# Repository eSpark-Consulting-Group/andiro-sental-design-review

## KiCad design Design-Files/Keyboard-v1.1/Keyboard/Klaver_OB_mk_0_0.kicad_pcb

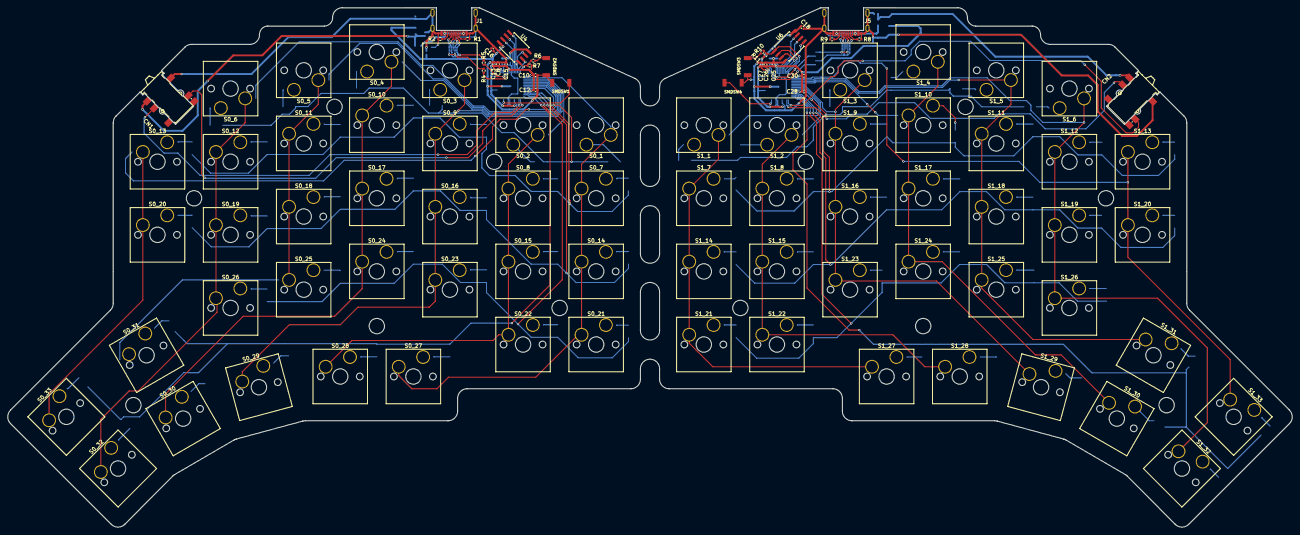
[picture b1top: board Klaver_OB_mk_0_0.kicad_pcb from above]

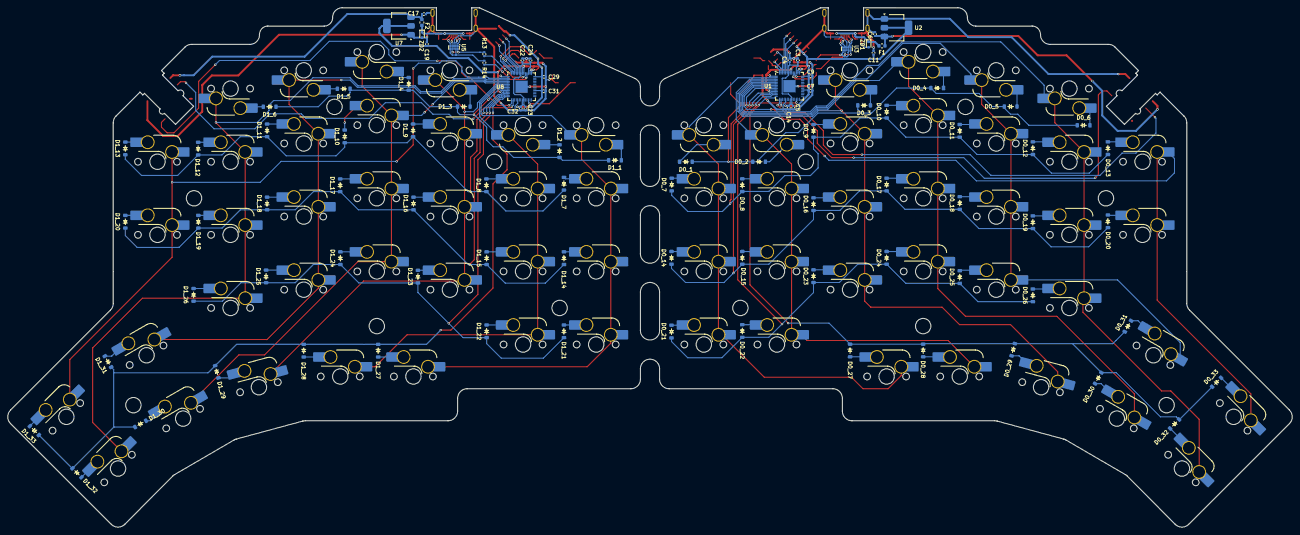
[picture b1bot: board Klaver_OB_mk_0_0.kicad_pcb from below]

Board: 2 copper layers, 334.7 x 135.3 mm, 192 parts (160 on the bottom side), 132 nets.

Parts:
C3, C4, C7, C9, C10, C12, C13, C14, C15, C22, C23, C25, C27, C28, C29, C30, C31, C32: 100n; C_0402_1005Metric
C5, C8, C16, C18, C24, C26: 1u; C_0402_1005Metric
C6, C11, C17, C19: 10u; C_0402_1005Metric
CN1, CN2: PJ-399F-6A; AUDIO-SMD_PJ-399F-6A
D0_1, D0_2, D0_3, D0_4, D0_5, D0_6, D0_7, D0_8, D0_9, D0_10, D0_11, D0_12, D0_13, D0_14, D0_15, D0_16, D0_17, D0_18, D0_19, D0_20, D0_21, D0_22, D0_23, D0_24, D0_25, D0_26, D0_27, D0_28, D0_29, D0_30, D0_31, D0_32, D0_33, D1_1, D1_2, D1_3, D1_4, D1_5, D1_6, D1_7, D1_8, D1_9, D1_10, D1_11, D1_12, D1_13, D1_14, D1_15, D1_16, D1_17, D1_18, D1_19, D1_20, D1_21, D1_22, D1_23, D1_24, D1_25, D1_26, D1_27, D1_28, D1_29, D1_30, D1_31, D1_32, D1_33: Diode; Diode_SOD-123
F1, F2: BSMD0603-050-12V; Fuse_0603_1608Metric
J1, J5: TYPE-C-31-M-13C
R1, R2, R8, R9: 5.1k; R_0402_1005Metric
R4, R5, R13, R14: 27; R_0402_1005Metric
R6, R10: 1k; R_0402_1005Metric
R7, R11: 10k; R_0402_1005Metric
S0_1, S0_2, S0_3, S0_4, S0_5, S0_6, S0_7, S0_8, S0_9, S0_10, S0_11, S0_12, S0_13, S0_14, S0_15, S0_16, S0_17, S0_18, S0_19, S0_20, S0_21, S0_22, S0_23, S0_24, S0_25, S0_26, S0_27, S0_28, S0_29, S0_30, S0_31, S0_32, S0_33, S1_1, S1_2, S1_3, S1_4, S1_5, S1_6, S1_7, S1_8, S1_9, S1_10, S1_11, S1_12, S1_13, S1_14, S1_15, S1_16, S1_17, S1_18, S1_19, S1_20, S1_21, S1_22, S1_23, S1_24, S1_25, S1_26, S1_27, S1_28, S1_29, S1_30, S1_31, S1_32, S1_33: Keyswitch; Hotswap_MX_Plated_1.00u
SMDSW1, SMDSW2, SMDSW3, SMDSW4: TS-1088R-02026
U1, U8: RP2040; QFN-56-1EP_7x7mm_P0.4mm_EP3.2x3.2mm
U2, U7: NCP1117LPST33T3G; SOT-223-3_TabPin2
U3, U5: TPD4E05U06DQAR; USON-10_2.5x1.0mm_P0.5mm
U4, U6: W25Q128JVSIQ; SOIC-8_5.23x5.23mm_P1.27mm
ZD1, ZD2: ESD5Z5V0C; D_SOD-523

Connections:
+1V1: C22.1, C23.1, C24.1, U8.23 (DVDD), U8.45 (VREG_VOUT), U8.50 (DVDD)
+1V1_0: C3.1, C4.1, C5.1, U1.23 (DVDD), U1.45 (VREG_VOUT), U1.50 (DVDD)
+3V3: C18.1, C19.1, C25.1, C26.1, C27.1, C28.1, C29.1, C30.1, C31.1, C32.1, R11.2, U6.8 (VCC), U7.2 (VO), U8.1 (IOVDD), U8.10 (IOVDD), U8.22 (IOVDD), U8.33 (IOVDD), U8.42 (IOVDD), U8.43 (ADC_AVDD), U8.44 (VREG_IN), U8.48 (USB_VDD), U8.49 (IOVDD)
+3V3_0: C7.1, C8.1, C9.1, C10.1, C11.1, C12.1, C13.1, C14.1, C15.1, C16.1, R7.2, U1.1 (IOVDD), U1.10 (IOVDD), U1.22 (IOVDD), U1.33 (IOVDD), U1.42 (IOVDD), U1.43 (ADC_AVDD), U1.44 (VREG_IN), U1.48 (USB_VDD), U1.49 (IOVDD), U2.2 (VO), U4.8 (VCC)
+5V: C17.1, CN2.2, F2.2, U7.3 (VI)
+5V_0: C6.1, CN1.2, F1.2, U2.3 (VI)
/D+: J5.A6 (D+), J5.B6 (D+), R13.1, U5.1 (D1+), U5.4 (D2+), U5.7 (NC), U5.10 (NC)
/D-: J5.A7 (D-), J5.B7 (D-), R14.2, U5.2 (D1-), U5.5 (D2-), U5.6 (NC), U5.9 (NC)
/D_0+: J1.A6 (D+), J1.B6 (D+), R4.1, U3.1 (D1+), U3.4 (D2+), U3.7 (NC), U3.10 (NC)
/D_0-: J1.A7 (D-), J1.B7 (D-), R5.2, U3.2 (D1-), U3.5 (D2-), U3.6 (NC), U3.9 (NC)
/QSPI_SCLK: U6.6 (CLK), U8.52 (QSPI_SCLK)
/QSPI_SCL_0K_0: U1.52 (QSPI_SCLK), U4.6 (CLK)
/QSPI_SD0: U6.5 (DI(IO0)), U8.53 (QSPI_SD0)
/QSPI_SD0_0: U1.53 (QSPI_SD0), U4.5 (DI(IO0))
/QSPI_SD1: U6.2 (DO(IO1)), U8.55 (QSPI_SD1)
/QSPI_SD1_0: U1.55 (QSPI_SD1), U4.2 (DO(IO1))
/QSPI_SD2: U6.3 (IO2), U8.54 (QSPI_SD2)
/QSPI_SD2_0: U1.54 (QSPI_SD2), U4.3 (IO2)
/QSPI_SD3: U6.7 (IO3), U8.51 (QSPI_SD3)
/QSPI_SD3_0: U1.51 (QSPI_SD3), U4.7 (IO3)
/QSPI_SS: R10.1, R11.1, U6.1 (~CS), U8.56 (QSPI_SS)
/QSPI_SS_0: R6.1, R7.1, U1.56 (QSPI_SS), U4.1 (~CS)
/RX: CN2.4, U8.15 (GPIO12)
/RX_0: CN1.3, U1.16 (GPIO13)
/TX: CN2.3, U8.16 (GPIO13)
/TX_0: CN1.4, U1.15 (GPIO12)
Col 0_0: S0_1.1, S0_7.1, S0_14.1, S0_21.1, S0_27.1, U1.2 (GPIO0)
Col 0_1: S0_2.1, S0_8.1, S0_15.1, S0_22.1, S0_28.1, U1.3 (GPIO1)
Col 0_2: S0_3.1, S0_9.1, S0_16.1, S0_23.1, S0_29.1, U1.4 (GPIO2)
Col 0_3: S0_4.1, S0_10.1, S0_17.1, S0_24.1, S0_30.1, U1.5 (GPIO3)
Col 0_4: S0_5.1, S0_11.1, S0_18.1, S0_25.1, S0_31.1, U1.6 (GPIO4)
Col 0_5: S0_6.1, S0_12.1, S0_19.1, S0_26.1, S0_32.1, U1.7 (GPIO5)
Col 0_6: S0_13.1, S0_20.1, S0_33.1, U1.8 (GPIO6)
Col 1_0: S1_1.1, S1_7.1, S1_14.1, S1_21.1, S1_27.1, U8.8 (GPIO6)
Col 1_1: S1_2.1, S1_8.1, S1_15.1, S1_22.1, S1_28.1, U8.7 (GPIO5)
Col 1_2: S1_3.1, S1_9.1, S1_16.1, S1_23.1, S1_29.1, U8.6 (GPIO4)
Col 1_3: S1_4.1, S1_10.1, S1_17.1, S1_24.1, S1_30.1, U8.5 (GPIO3)
Col 1_4: S1_5.1, S1_11.1, S1_18.1, S1_25.1, S1_31.1, U8.4 (GPIO2)
Col 1_5: S1_6.1, S1_12.1, S1_19.1, S1_26.1, S1_32.1, U8.3 (GPIO1)
Col 1_6: S1_13.1, S1_20.1, S1_33.1, U8.2 (GPIO0)
GND: C17.2, C18.2, C19.2, C22.2, C23.2, C24.2, C25.2, C26.2, C27.2, C28.2, C29.2, C30.2, C31.2, C32.2, CN2.1, J5.A1 (GND), J5.A12 (GND), J5.B1 (GND), J5.B12 (GND), J5.S1 (SHIELD), R8.1, R9.1, SMDSW3.1, SMDSW4.1, U5.3 (GND), U5.8 (GND), U6.4 (GND), U7.1 (GND), U8.19 (TESTEN), U8.57 (GND), ZD2.2 (A)
GND_0: C3.2, C4.2, C5.2, C6.2, C7.2, C8.2, C9.2, C10.2, C11.2, C12.2, C13.2, C14.2, C15.2, C16.2, CN1.1, J1.A1 (GND), J1.A12 (GND), J1.B1 (GND), J1.B12 (GND), J1.S1 (SHIELD), R1.1, R2.1, SMDSW1.1, SMDSW2.1, U1.19 (TESTEN), U1.57 (GND), U2.1 (GND), U3.3 (GND), U3.8 (GND), U4.4 (GND), ZD1.2 (A)
unnamed: D0_1.2 (A), S0_1.2
unnamed: D0_2.2 (A), S0_2.2
unnamed: D0_3.2 (A), S0_3.2
unnamed: D0_4.2 (A), S0_4.2
unnamed: D0_5.2 (A), S0_5.2
unnamed: D0_6.2 (A), S0_6.2
unnamed: D0_7.2 (A), S0_7.2
unnamed: D0_8.2 (A), S0_8.2
unnamed: D0_9.2 (A), S0_9.2
unnamed: D0_10.2 (A), S0_10.2
unnamed: D0_11.2 (A), S0_11.2
unnamed: D0_12.2 (A), S0_12.2
unnamed: D0_13.2 (A), S0_13.2
unnamed: D0_14.2 (A), S0_14.2
unnamed: D0_15.2 (A), S0_15.2
unnamed: D0_16.2 (A), S0_16.2
unnamed: D0_17.2 (A), S0_17.2
unnamed: D0_18.2 (A), S0_18.2
unnamed: D0_19.2 (A), S0_19.2
unnamed: D0_20.2 (A), S0_20.2
unnamed: D0_21.2 (A), S0_21.2
unnamed: D0_22.2 (A), S0_22.2
unnamed: D0_23.2 (A), S0_23.2
unnamed: D0_24.2 (A), S0_24.2
unnamed: D0_25.2 (A), S0_25.2
unnamed: D0_26.2 (A), S0_26.2
unnamed: D0_27.2 (A), S0_27.2
unnamed: D0_28.2 (A), S0_28.2
unnamed: D0_29.2 (A), S0_29.2
unnamed: D0_30.2 (A), S0_30.2
unnamed: D0_31.2 (A), S0_31.2
unnamed: D0_32.2 (A), S0_32.2
unnamed: D0_33.2 (A), S0_33.2
unnamed: D1_1.2 (A), S1_1.2
unnamed: D1_2.2 (A), S1_2.2
unnamed: D1_3.2 (A), S1_3.2
unnamed: D1_4.2 (A), S1_4.2
unnamed: D1_5.2 (A), S1_5.2
unnamed: D1_6.2 (A), S1_6.2
unnamed: D1_7.2 (A), S1_7.2
unnamed: D1_8.2 (A), S1_8.2
unnamed: D1_9.2 (A), S1_9.2
unnamed: D1_10.2 (A), S1_10.2
unnamed: D1_11.2 (A), S1_11.2
unnamed: D1_12.2 (A), S1_12.2
unnamed: D1_13.2 (A), S1_13.2
unnamed: D1_14.2 (A), S1_14.2
unnamed: D1_15.2 (A), S1_15.2
unnamed: D1_16.2 (A), S1_16.2
unnamed: D1_17.2 (A), S1_17.2
unnamed: D1_18.2 (A), S1_18.2
unnamed: D1_19.2 (A), S1_19.2
unnamed: D1_20.2 (A), S1_20.2
unnamed: D1_21.2 (A), S1_21.2
unnamed: D1_22.2 (A), S1_22.2
unnamed: D1_23.2 (A), S1_23.2
unnamed: D1_24.2 (A), S1_24.2
unnamed: D1_25.2 (A), S1_25.2
unnamed: D1_26.2 (A), S1_26.2
unnamed: D1_27.2 (A), S1_27.2
unnamed: D1_28.2 (A), S1_28.2
unnamed: D1_29.2 (A), S1_29.2
unnamed: D1_30.2 (A), S1_30.2
unnamed: D1_31.2 (A), S1_31.2
unnamed: D1_32.2 (A), S1_32.2
unnamed: D1_33.2 (A), S1_33.2
unnamed: J1.A5 (CC1), R1.2
unnamed: J1.B5 (CC2), R2.2
unnamed: J5.A5 (CC1), R8.2
unnamed: J5.B5 (CC2), R9.2
unnamed: R6.2, SMDSW2.2
unnamed: R10.2, SMDSW3.2
unnamed: SMDSW1.2, U1.26 (RUN)
unnamed: R5.1, U1.46 (USB_DM)
unnamed: R4.2, U1.47 (USB_DP)
unnamed: SMDSW4.2, U8.26 (RUN)
unnamed: R14.1, U8.46 (USB_DM)
unnamed: R13.2, U8.47 (USB_DP)
Row 0_0: D0_1.1 (K), D0_2.1 (K), D0_3.1 (K), D0_4.1 (K), D0_5.1 (K), D0_6.1 (K), U1.9 (GPIO7)
Row 0_1: D0_7.1 (K), D0_8.1 (K), D0_9.1 (K), D0_10.1 (K), D0_11.1 (K), D0_12.1 (K), D0_13.1 (K), U1.11 (GPIO8)
Row 0_2: D0_14.1 (K), D0_15.1 (K), D0_16.1 (K), D0_17.1 (K), D0_18.1 (K), D0_19.1 (K), D0_20.1 (K), U1.12 (GPIO9)
Row 0_3: D0_21.1 (K), D0_22.1 (K), D0_23.1 (K), D0_24.1 (K), D0_25.1 (K), D0_26.1 (K), U1.13 (GPIO10)
Row 0_4: D0_27.1 (K), D0_28.1 (K), D0_29.1 (K), D0_30.1 (K), D0_31.1 (K), D0_32.1 (K), D0_33.1 (K), U1.14 (GPIO11)
Row 1_0: D1_1.1 (K), D1_2.1 (K), D1_3.1 (K), D1_4.1 (K), D1_5.1 (K), D1_6.1 (K), U8.9 (GPIO7)
Row 1_1: D1_7.1 (K), D1_8.1 (K), D1_9.1 (K), D1_10.1 (K), D1_11.1 (K), D1_12.1 (K), D1_13.1 (K), U8.11 (GPIO8)
Row 1_2: D1_14.1 (K), D1_15.1 (K), D1_16.1 (K), D1_17.1 (K), D1_18.1 (K), D1_19.1 (K), D1_20.1 (K), U8.12 (GPIO9)
Row 1_3: D1_21.1 (K), D1_22.1 (K), D1_23.1 (K), D1_24.1 (K), D1_25.1 (K), D1_26.1 (K), U8.13 (GPIO10)
Row 1_4: D1_27.1 (K), D1_28.1 (K), D1_29.1 (K), D1_30.1 (K), D1_31.1 (K), D1_32.1 (K), D1_33.1 (K), U8.14 (GPIO11)
VBUS: F2.1, J5.A4 (VBUS), J5.A9 (VBUS), J5.B4 (VBUS), J5.B9 (VBUS), ZD2.1 (K)
VBUS_0: F1.1, J1.A4 (VBUS), J1.A9 (VBUS), J1.B4 (VBUS), J1.B9 (VBUS), ZD1.1 (K)

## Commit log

2024-07-25 Client files pushed
2024-07-25 added pdf files
2024-08-06 #3 gitignore added. Schematic folder added
2024-08-06 #3 added resistor on i2c and added tvs diode
2024-08-06 #3 added resistors on i2c bus added tvs diodes and on data bus for addressable leds
2024-08-07 #3 done all changes in schematic except placement of sata connector
2024-08-08 #3 all schematic changes done
2024-08-08 #3 sata update
2024-08-09 gitignore line added to remove KiCad backup files
2024-08-09 more info added to gitignore
2024-08-09 #3 swaped TX RX, Fuse updated
2024-08-09 #3 Schematic PDF file
2024-08-09 PDF location updated
2024-08-22 #3 changed trrs connector and added zener diodes
2024-08-22 #3 corrected TX RX
